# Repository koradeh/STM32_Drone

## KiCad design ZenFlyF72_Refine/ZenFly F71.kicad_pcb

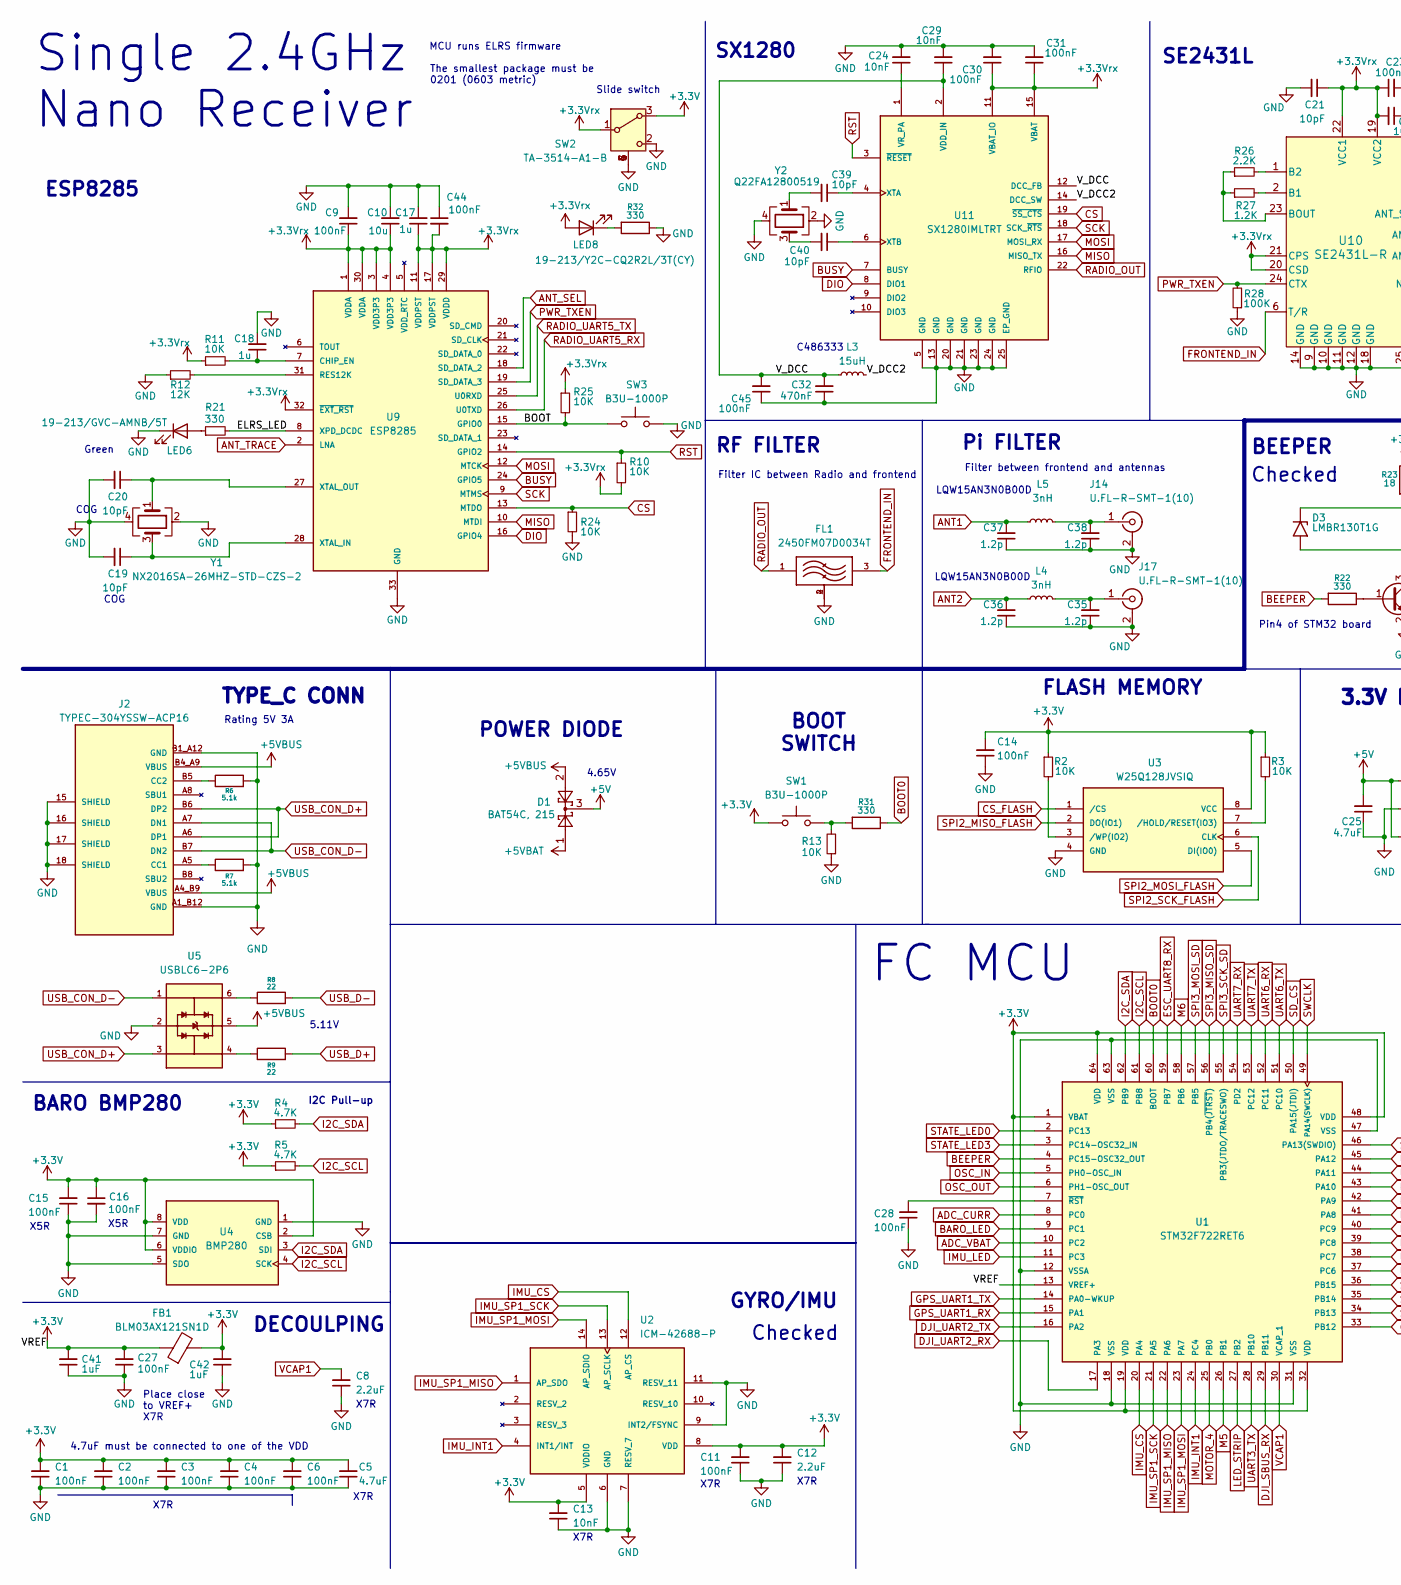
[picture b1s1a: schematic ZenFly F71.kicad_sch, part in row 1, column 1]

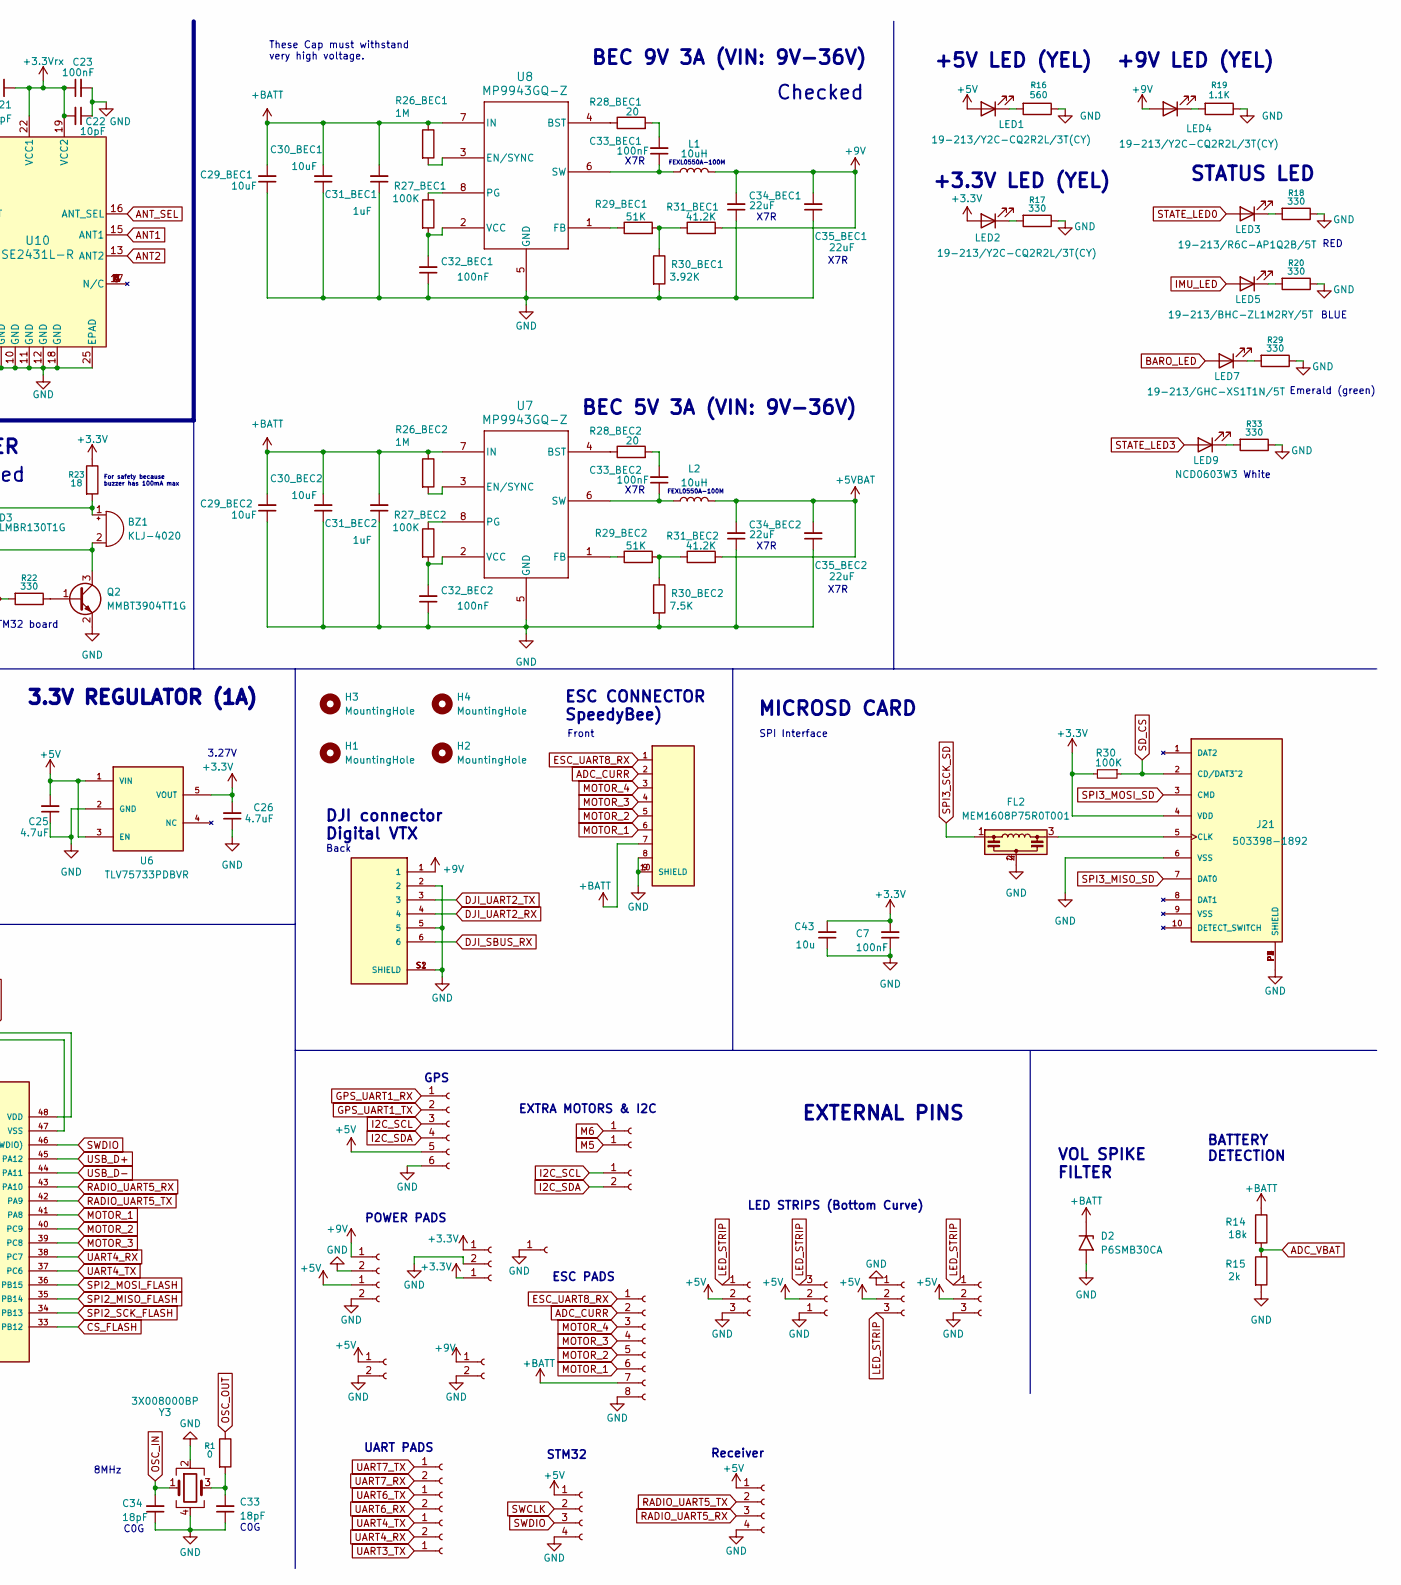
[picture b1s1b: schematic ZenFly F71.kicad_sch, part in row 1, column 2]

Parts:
BZ1: KLJ-4020
C1, C2, C3, C4, C6, C7, C9, C11, C14, C15, C16, C23, C27, C28, C30, C31, C33_BEC1, C33_BEC2, C44, C45: 100nF; C_0201_0603Metric
C5, C25, C26: 4.7uF; C_0603_1608Metric
C8, C12: 2.2uF; C_0402_1005Metric
C10, C43: 10u; C_0603_1608Metric
C13, C24, C29: 10nF; C_0201_0603Metric
C17, C18: 1u; C_0402_1005Metric
C19, C20, C21, C22, C39, C40: 10pF; C_0201_0603Metric
C29_BEC1, C29_BEC2, C30_BEC1, C30_BEC2: 10uF; C_0805_2012Metric
C31_BEC1, C31_BEC2, C41, C42: 1uF; C_0402_1005Metric
C32: 470nF; C_0402_1005Metric
C32_BEC1, C32_BEC2: 100nF; C_0402_1005Metric
C33, C34: 18pF; C_0201_0603Metric
C34_BEC1, C35_BEC1: 22uF; C_0603_1608Metric
C34_BEC2, C35_BEC2: 22uF; C_0402_1005Metric
C35, C36, C37, C38: 1.2p; C_0201_0603Metric
D1: BAT54C, 215; SMD-DIODE-SCHOTTKY-30V-200MA_SOT-23
D2: P6SMB30CA; D_SMB
D3: LMBR130T1G; D_SOD-123
FB1: BLM03AX121SN1D; C_0201_0603Metric
FL1: 2450FM07D0034T; PARTREV 1.2
FL2: MEM1608P75R0T001
H1, H2, H3, H4: MountingHole; MountingHole_3.2mm_M3
J1, J6, J9, J10, J13, J22, J23, J25, J27: Conn_01x02_Socket; SMD_2Pads_Small
J2: TYPEC-304YSSW-ACP16; TYPEC-304-ACP16_XNP; PARTREV A
J3, J18, J19, J20: Conn_01x03_Socket; SMD_3Pads_41mmCurve
J4: SM06B-SRSS-TB_LF__SN_; JST_SM06B-SRSS-TB_LF__SN_
J5, J7: Conn_01x04_Socket; SMD_4Pads_Small
J8: SM08B-SRSS-TB_LF__SN_; SM08B-SRSS-TB_LF_SN
J11: Conn_01x06_Socket; SMD_6Pads_Small
J12, J15, J24, J26, J28: Conn_01x01_Socket; SMD_1Pad_Small
J14, J17: U.FL-R-SMT-1(10); U.FL_Hirose_U.FL-R-SMT-1_Vertical
J16: Conn_01x08_Socket; SMD_8Pads_Small
J21: 503398-1892; MOLEX_503398-1892; PARTREV 0
L1, L2: 10uH; FEXL0550A-100M
L3: 15uH; L_0805_2012Metric
L4, L5: 3nH; L_0402_1005Metric
LED1, LED2, LED4, LED8: 19-213/Y2C-CQ2R2L/3T(CY); LED_0603
LED3: 19-213/R6C-AP1Q2B/5T; LED_0603
LED5: 19-213/BHC-ZL1M2RY/5T; LED_0603
LED6: 19-213/GVC-AMNB/5T; LED_0603
LED7: 19-213/GHC-XS1T1N/5T; LED_0603
LED9: NCD0603W3; LED_0603
Q2: MMBT3904TT1G; TRANS_MMBT3904TT1G
R1: 0; R_0201_0603Metric
R2, R3, R10, R11, R13, R24, R25: 10K; R_0201_0603Metric
R4, R5: 4.7K; R_0201_0603Metric
R6, R7: 5.1k; R_0402_1005Metric
R8, R9: 22; R_0201_0603Metric
R12: 12K; R_0402_1005Metric
R14: 18k; R_0402_1005Metric
R15: 2k; R_0201_0603Metric
R16: 560; R_0201_0603Metric
R17, R18, R20, R21, R22, R29, R31, R32, R33: 330; R_0201_0603Metric
R19: 1.1K; R_0201_0603Metric
R23: 18; R_0201_0603Metric
R26: 2.2K; R_0201_0603Metric
R26_BEC1, R26_BEC2: 1M; R_0402_1005Metric
R27: 1.2K; R_0201_0603Metric
R27_BEC1, R27_BEC2: 100K; R_0402_1005Metric
R28, R30: 100K; R_0201_0603Metric
R28_BEC1, R28_BEC2: 20; R_0402_1005Metric
R29_BEC1, R29_BEC2: 51K; R_0402_1005Metric
R30_BEC1: 3.92K; R_0402_1005Metric
R30_BEC2: 7.5K; R_0402_1005Metric
R31_BEC1, R31_BEC2: 41.2K; R_0402_1005Metric
SW1, SW3: B3U-1000P; SW_B3U-1000P
SW2: TA-3514-A1-B; Slide Switch TA-3514-A1-B
U1: STM32F722RET6
U2: ICM-42688-P; PARTREV 1.2
U3: W25Q128JVSIQ; SOIC127P790X216-8N; PARTREV I
U4: BMP280; XDCR_BMP280; PART_REV 1.19
U5: USBLC6-2P6; PARTREV 5
U6: TLV75733PDBVR; PARTREV Aprill 2011
U7, U8: MP9943GQ-Z; QFN-8_MP9943_MNP
U9: ESP8285; QFN50P500X500X90-33N; PARTREV 2.0
U10: SE2431L-R; SE2431L_SKY-L
U11: SX1280IMLTRT; XCVR_SX1280IMLTRT; PARTREV 3.3
Y1: NX2016SA-26MHZ-STD-CZS-2; Crystal_SMD_2016-4Pin_2.0x1.6mm
Y2: Q22FA12800519; Crystal_SMD_2016-4Pin_2.0x1.6mm
Y3: 3X008000BP; Crystal_SMD_3225-4Pin_3.2x2.5mm

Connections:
+3.3V: C1.2, C2.2, C3.2, C4.2, C5.2, C6.2, C7.2, C11.2, C12.2, C13.2, C14.2, C15.2, C16.1, C26.2, C27.2, C41.2, C42.2, C43.2, FB1.1, FB1.2, J10.1, J15.1, J21.4 (VDD), LED2.E, R2.1, R3.1, R4.1, R5.1, R23.1, R30.2, SW1.1, SW2.3 (A), U1.1 (VBAT), U1.13 (VREF+), U1.19 (VDD), U1.32 (VDD), U1.48 (VDD), U1.64 (VDD), U2.5 (VDDIO), U2.8 (VDD), U3.8 (VCC), U4.2 (CSB), U4.6 (VDDIO), U4.8 (VDD), U6.5 (VOUT)
+3.3Vrx: C9.1, C10.1, C17.1, C21.1, C22.2, C23.1, C30.1, C31.1, C44.2, LED8.E, R10.2, R11.1, R25.1, SW2.1 (B), U9.1 (VDDA), U9.3 (VDD3P3), U9.4 (VDD3P3), U9.11 (VDDPST), U9.17 (VDDPST), U9.29 (VDDD), U9.30 (VDDA), U9.32 (~EXT_RST), U10.19 (VCC2), U10.20 (CSD), U10.21 (CPS), U10.22 (VCC1), U11.11 (VBAT_IO), U11.15 (VBAT)
+5V: C25.2, D1.3, J3.2, J5.1, J7.1, J11.5, J13.1, J18.2, J19.2, J20.2, J27.1, LED1.E, U6.1 (VIN), U6.3 (EN)
+5VBAT: C34_BEC2.2, C35_BEC2.2, D1.1, L2.2, R31_BEC2.2
+5VBUS: D1.2, J2.A4_B9 (VBUS), J2.B4_A9 (VBUS), U5.5
+9V: C34_BEC1.2, C35_BEC1.2, J4.1, J6.1, J22.1, L1.2, LED4.E, R31_BEC1.2
+BATT: C29_BEC1.2, C29_BEC2.2, C30_BEC1.2, C30_BEC2.2, C31_BEC1.2, C31_BEC2.2, D2.1 (A1), J8.7, J16.7, R14.1, R26_BEC1.1, R26_BEC2.1, U7.7 (IN), U8.7 (IN)
/BOOT: R25.2, SW3.1, U9.15 (GPIO0)
/ELRS_LED: R21.2, U9.8 (XPD_DCDC)
/V_DCC: C29.1, C32.2, C45.2, L3.1, U11.2 (VDD_IN), U11.12 (DCC_FB)
/V_DCC2: L3.2, U11.14 (DCC_SW)
ADC_CURR: J8.2, J16.2, U1.8 (PC0)
ADC_VBAT: R14.2, R15.1, U1.10 (PC2)
ANT1: C37.2, L5.1, U10.15 (ANT1)
ANT2: C36.2, L4.1, U10.13 (ANT2)
ANT_SEL: U9.18 (SD_DATA_2), U10.16 (ANT_SEL)
ANT_TRACE: U9.2 (LNA)
BARO_LED: LED7.E, U1.9 (PC1)
BEEPER: R22.2, U1.4 (PC15-OSC32_OUT)
BOOT0: R31.1, U1.60 (BOOT)
BUSY: U9.24 (GPIO5), U11.7 (BUSY)
CS: R24.1, U9.13 (MTDO), U11.19 (~SS_CTS)
CS_FLASH: U1.33 (PB12), U3.1 (/CS)
DIO: U9.16 (GPIO4), U11.8 (DIO1)
DJI_SBUS_RX: J4.6, U1.29 (PB11)
DJI_UART2_RX: J4.4, U1.17 (PA3)
DJI_UART2_TX: J4.3, U1.16 (PA2)
ESC_UART8_RX: J8.1, J16.1, U1.59 (PB7)
FRONTEND_IN: FL1.3, U10.6 (T/R)
GND: C1.1, C2.1, C3.1, C4.1, C5.1, C6.1, C7.1, C8.1, C9.2, C10.2, C11.1, C12.1, C13.1, C14.1, C15.1, C16.2, C17.2, C18.2, C19.2, C20.2, C21.2, C22.1, C23.2, C24.2, C25.1, C26.1, C27.1, C28.1, C29.2, C29_BEC1.1, C29_BEC2.1, C30.2, C30_BEC1.1, C30_BEC2.1, C31.2, C31_BEC1.1, C31_BEC2.1, C32.1, C32_BEC1.1, C32_BEC2.1, C33.1, C34.1, C34_BEC1.1, C34_BEC2.1, C35.1, C35_BEC1.1, C35_BEC2.1, C36.1, C37.1, C38.1, C41.1, C42.1, C43.1, C44.1, C45.1, D2.2 (A2), FL1.2, FL1.4, FL2.2, FL2.4, J2.15 (SHIELD), J2.16 (SHIELD), J2.17 (SHIELD), J2.18 (SHIELD), J2.A1_B12 (GND), J2.B1_A12 (GND), J3.1, J4.2, J4.5, J4.S1 (SHIELD), J4.S2 (SHIELD), J5.4, J6.2, J7.4, J8.8, J8.9 (SHIELD), J8.10 (SHIELD), J10.2, J11.6, J12.1, J13.2, J14.2 (Ext), J16.8, J17.2 (Ext), J18.3, J19.3, J20.1, J21.6 (VSS), J21.P1 (SHIELD), J21.P2 (SHIELD), J21.P3 (SHIELD), J21.P4 (SHIELD), J22.2, J27.2, LED6.C, Q2.2 (E), R6.2, R7.2, R12.1, R13.1, R15.2, R16.1, R17.1, R18.1, R19.1, R20.1, R24.2, R28.1, R29.1, R30_BEC1.2, R30_BEC2.2, R32.1, R33.1, SW2.2 (C), SW2.4 (G), SW2.5 (G), SW2.6 (G), SW2.7 (G), SW3.2, U1.12 (VSSA), U1.18 (VSS), U1.31 (VSS), U1.47 (VSS), U1.63 (VSS), U2.6 (GND), U2.7 (RESV_7), U2.9 (INT2/FSYNC), U2.11 (RESV_11), U3.4 (GND), U4.1 (GND), U4.5 (SDO), U4.7 (GND), U5.2, U6.2 (GND), U7.5 (GND), U8.5 (GND), U9.33 (GND), U10.9 (GND), U10.10 (GND), U10.11 (GND), U10.12 (GND), U10.14 (GND), U10.18 (GND), U10.25 (EPAD), U11.5 (GND), U11.13 (GND), U11.20 (GND), U11.21 (GND), U11.23 (GND), U11.24 (GND), U11.25 (EP_GND), Y1.2, Y1.4, Y2.2, Y2.4, Y3.2, Y3.4
GPS_UART1_RX: J11.1, U1.15 (PA1)
GPS_UART1_TX: J11.2, U1.14 (PA0-WKUP)
I2C_SCL: J1.1, J11.3, R5.2, U1.61 (PB8), U4.4 (SCK)
I2C_SDA: J1.2, J11.4, R4.2, U1.62 (PB9), U4.3 (SDI)
IMU_CS: U1.20 (PA4), U2.12 (AP_CS)
IMU_INT1: U1.24 (PC4), U2.4 (INT1/INT)
IMU_LED: LED5.E, U1.11 (PC3)
IMU_SP1_MISO: U1.22 (PA6), U2.1 (AP_SDO)
IMU_SP1_MOSI: U1.23 (PA7), U2.14 (AP_SDIO)
IMU_SP1_SCK: U1.21 (PA5), U2.13 (AP_SCLK)
LED_STRIP: J3.3, J18.1, J19.1, J20.3, U1.27 (PB2)
M5: J28.1, U1.26 (PB1)
M6: J24.1, U1.58 (PB6)
MISO: U9.10 (MTDI), U11.16 (MISO_TX)
MOSI: U9.12 (MTCK), U11.17 (MOSI_RX)
MOTOR_1: J8.6, J16.6, U1.41 (PA8)
MOTOR_2: J8.5, J16.5, U1.40 (PC9)
MOTOR_3: J8.4, J16.4, U1.39 (PC8)
MOTOR_4: J8.3, J16.3, U1.25 (PB0)
unnamed: BZ1.1 (+), D3.1 (A1), R23.2
unnamed: BZ1.2 (-), D3.2 (A2), Q2.3 (C)
unnamed: C33.2, R1.2, Y3.3
unnamed: C33_BEC1.2, R28_BEC1.2
unnamed: C33_BEC2.2, R28_BEC2.2
unnamed: C39.2, Y2.1
unnamed: C40.2, Y2.3
unnamed: J2.A5 (CC1), R7.1
unnamed: J2.B5 (CC2), R6.1
unnamed: C38.2, J14.1 (In), L5.2
unnamed: C35.2, J17.1 (In), L4.2
unnamed: FL2.3, J21.5 (CLK)
unnamed: LED1.C, R16.2
unnamed: LED2.C, R17.2
unnamed: LED3.C, R18.2
unnamed: LED4.C, R19.2
unnamed: LED5.C, R20.2
unnamed: LED6.E, R21.1
unnamed: LED7.C, R29.2
unnamed: LED8.C, R32.2
unnamed: LED9.C, R33.2
unnamed: Q2.1 (B), R22.1
unnamed: R8.1, U5.6
unnamed: R9.1, U5.4
unnamed: R13.2, R31.2, SW1.2
unnamed: R29_BEC1.2, R30_BEC1.1, R31_BEC1.1
unnamed: R29_BEC2.2, R30_BEC2.1, R31_BEC2.1
unnamed: C28.2, U1.7 (~RST)
unnamed: R3.2, U3.7 (/HOLD/RESET(IO3))
unnamed: R2.2, U3.3 (/WP(IO2))
unnamed: R28_BEC2.1, U7.4 (BST)
unnamed: R26_BEC2.2, U7.3 (EN/SYNC)
unnamed: R29_BEC2.1, U7.1 (FB)
unnamed: R27_BEC2.1, U7.8 (PG)
unnamed: C33_BEC2.1, L2.1, U7.6 (SW)
unnamed: C32_BEC2.2, R27_BEC2.2, U7.2 (VCC)
unnamed: R28_BEC1.1, U8.4 (BST)
unnamed: R26_BEC1.2, U8.3 (EN/SYNC)
unnamed: R29_BEC1.1, U8.1 (FB)
unnamed: R27_BEC1.1, U8.8 (PG)
unnamed: C33_BEC1.1, L1.1, U8.6 (SW)
unnamed: C32_BEC1.2, R27_BEC1.2, U8.2 (VCC)
unnamed: C18.1, R11.2, U9.7 (CHIP_EN)
unnamed: R12.2, U9.31 (RES12K)
unnamed: C19.1, U9.28 (XTAL_IN), Y1.3
unnamed: C20.1, U9.27 (XTAL_OUT), Y1.1
unnamed: R27.2, U10.2 (B1)
unnamed: R26.2, U10.1 (B2)
unnamed: R26.1, R27.1, U10.23 (BOUT)
unnamed: C24.1, U11.1 (VR_PA)
unnamed: C39.1, U11.4 (XTA)
unnamed: C40.1, U11.6 (XTB)
OSC_IN: C34.2, U1.5 (PH0-OSC_IN), Y3.1
OSC_OUT: R1.1, U1.6 (PH1-OSC_OUT)
PWR_TXEN: R28.2, U9.19 (SD_DATA_3), U10.24 (CTX)
RADIO_OUT: FL1.1, U11.22 (RFIO)
RADIO_UART5_RX: J5.3, U1.43 (PA10), U9.26 (U0TXD)
RADIO_UART5_TX: J5.2, U1.42 (PA9), U9.25 (U0RXD)
RST: R10.1, U9.14 (GPIO2), U11.3 (~RESET)
SCK: U9.9 (MTMS), U11.18 (SCK_~RTS)
SD_CS: J21.2 (CD/DAT3^2), R30.1, U1.50 (PA15(JTDI))
SPI2_MISO_FLASH: U1.35 (PB14), U3.2 (DO(IO1))
SPI2_MOSI_FLASH: U1.36 (PB15), U3.5 (DI(IO0))
SPI2_SCK_FLASH: U1.34 (PB13), U3.6 (CLK)
SPI3_MISO_SD: J21.7 (DAT0), U1.56 (PB4(~JTRST))
SPI3_MOSI_SD: J21.3 (CMD), U1.57 (PB5)
SPI3_SCK_SD: FL2.1, U1.55 (PB3(JTDO/TRACESWO))
STATE_LED0: LED3.E, U1.2 (PC13)
STATE_LED3: LED9.E, U1.3 (PC14-OSC32_IN)
SWCLK: J7.2, U1.49 (PA14(SWCLK))
SWDIO: J7.3, U1.46 (PA13(SWDIO))
UART3_TX: J26.1, U1.28 (PB10)
UART4_RX: J25.2, U1.38 (PC7)
UART4_TX: J25.1, U1.37 (PC6)
UART6_RX: J23.2, U1.52 (PC11)
UART6_TX: J23.1, U1.51 (PC10)
UART7_RX: J9.2, U1.54 (PD2)
UART7_TX: J9.1, U1.53 (PC12)
USB_CON_D+: J2.A6 (DP1), J2.B6 (DP2), U5.3
USB_CON_D-: J2.A7 (DN1), J2.B7 (DN2), U5.1
USB_D+: R9.2, U1.45 (PA12)
USB_D-: R8.2, U1.44 (PA11)
VCAP1: C8.2, U1.30 (VCAP_1)

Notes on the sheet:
LQW15AN3N0B00D
Rating 5V 3A
ESC CONNECTOR SpeedyBee)
Checked
X7R
Pin4 of STM32 board
+3.3V LED (YEL)
UART PADS
Single 2.4GHz Nano Receiver
BLUE
Place close to VREF+ X7R
RF FILTER
STM32
SX1280
FEXL0550A-100M
SE2431L
C486333
STATUS LED
White
X5R
BEC 5V 3A (VIN: 9V-36V)
Back
These Cap must withstand very high voltage.
LED STRIPS (Bottom Curve)
Filter IC between Radio and frontend
Emerald (green)
EXTERNAL PINS
BEC 9V 3A (VIN: 9V-36V)
C0G
COG
5.11V
POWER DIODE
Receiver
4.65V
BOOT SWITCH
Front
DECOULPING
GPS
+9V LED (YEL)
Filter between frontend and antennas

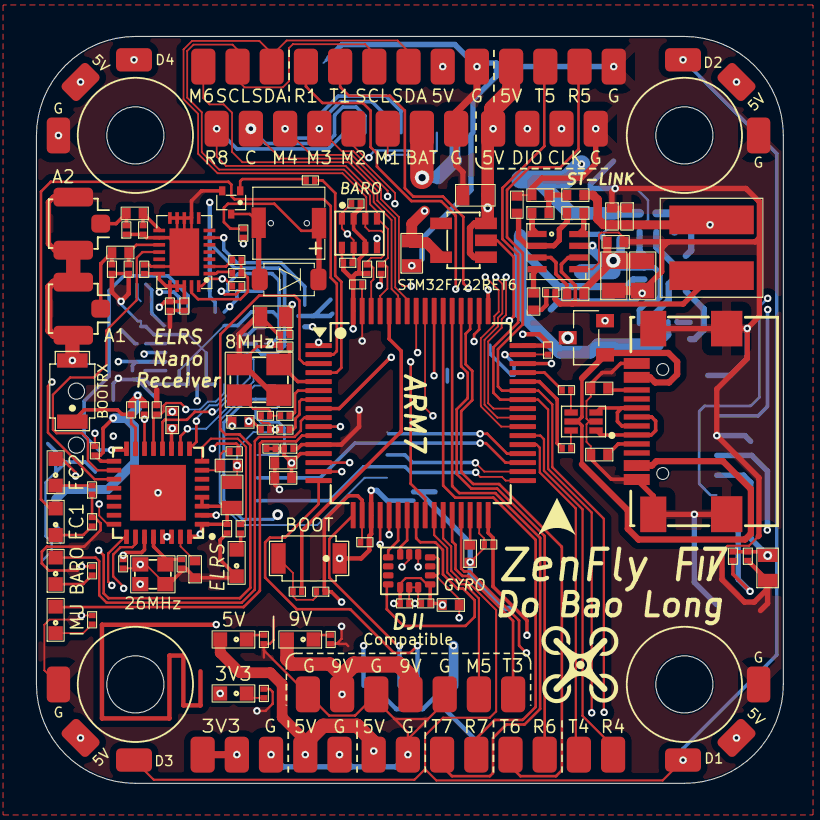
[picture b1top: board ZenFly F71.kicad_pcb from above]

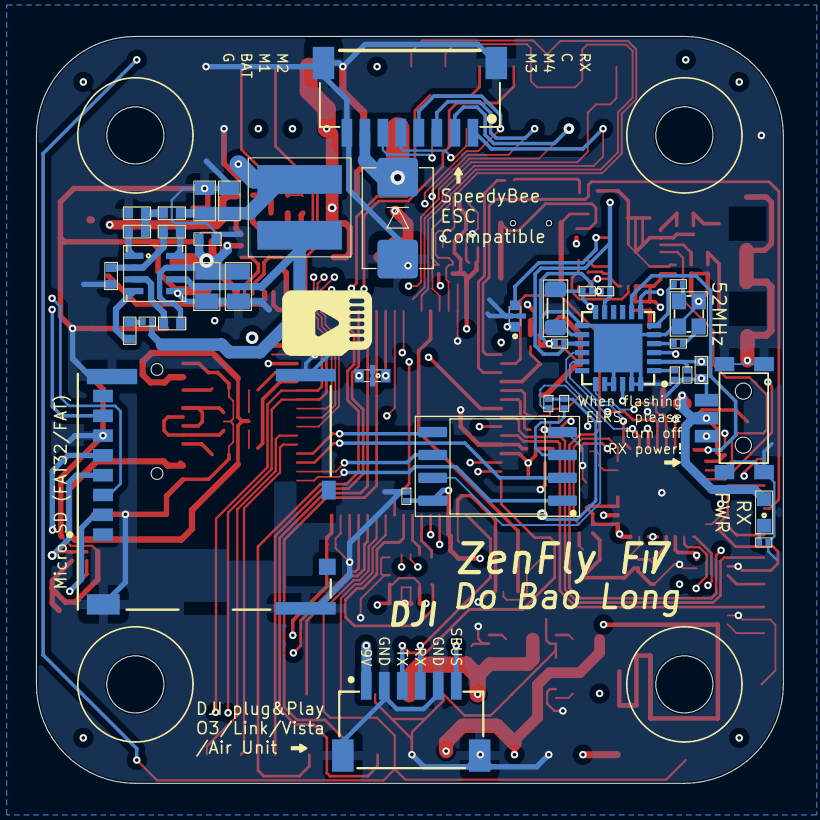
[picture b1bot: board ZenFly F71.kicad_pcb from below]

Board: 4 copper layers, 41.5 x 41.5 mm, 175 parts (39 on the bottom side), 131 nets.

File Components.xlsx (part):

Resistor | Value | LCSC | Footprint | Spec
R1 | 0 | None | #0201 | None
R2 | 10K | C319932 | #0201 | 1/32W Thin Film Resistor 15V ±0.5% ±50ppm/℃ 10kΩ 0201 Chip Resistor - Surface M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
R3 | 10K | C319932 | #0201 | 1/32W Thin Film Resistor 15V ±0.5% ±50ppm/℃ 10kΩ 0201 Chip Resistor - Surface M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
R4 | 4.7K | C852254 | #0201 | 50mW Thin Film Resistor ±25ppm/℃ ±0.1% 4.7kΩ 0201 Chip Resistor - Surface Mount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
R5 | 4.7K | C852254 | #0201 | 50mW Thin Film Resistor ±25ppm/℃ ±0.1% 4.7kΩ 0201 Chip Resistor - Surface Mount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
R6 | 5.1K | C851767 | #0402 | 50mW Thick Film Resistors ±0.5% ±200ppm/℃ 5.1kΩ 0201 Chip Resistor - Surface Mo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
R7 | 5.1K | C851767 | #0201 | 50mW Thick Film Resistors ±0.5% ±200ppm/℃ 5.1kΩ 0201 Chip Resistor - Surface Mo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
R8 | 22 | C2991382 | #0201 | 1/20W Thick Film Resistors 25V ±100ppm/℃ ±1% 22Ω 0201 Chip Resistor - Surface M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
R9 | 22 | C2991382 | #0201 | 1/20W Thick Film Resistors 25V ±100ppm/℃ ±1% 22Ω 0201 Chip Resistor - Surface M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
R10 | 10K | C319932 | #0201 | 1/32W Thin Film Resistor 15V ±0.5% ±50ppm/℃ 10kΩ 0201 Chip Resistor - Surface M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
R11 | 10K | C319932 | #0201 | 1/32W Thin Film Resistor 15V ±0.5% ±50ppm/℃ 10kΩ 0201 Chip Resistor - Surface M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
R12 | 12K | C2693077 | #0402 | 50mW 25V ±100ppm/℃ ±1% 12kΩ 0201 Chip Resistor - Surface Mount ROHS
R13 | 10K | C319932 | #0201 | 1/32W Thin Film Resistor 15V ±0.5% ±50ppm/℃ 10kΩ 0201 Chip Resistor - Surface M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
R14 | 18K | C246974 | #0402 | 1/16W Thin Film Resistor 50V ±25ppm/℃ ±0.1% 18kΩ 0402 Chip Resistor - Surface M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
R15 | 2K | C490810 | #0201 | 0.05W Thin Film Resistor 25V ±0.1% ±25ppm/℃ 2kΩ 0201 Chip Resistor - Surface Mo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
R16 | 560 | C490810 | #0201 | 0.05W Thin Film Resistor 25V ±0.1% ±25ppm/℃ 2kΩ 0201 Chip Resistor - Surface Mo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
R17 | 330 | C274872 | #0201 | 50mW Thick Film Resistors 25V ±1% ±200ppm/℃ 330Ω 0201 Chip Resistor - Surface M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
R18 | 330 | C274872 | #0201 | 50mW Thick Film Resistors 25V ±1% ±200ppm/℃ 330Ω 0201 Chip Resistor - Surface M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
R19 | 1.1K | C490809 | #0201 | 0.05W Thin Film Resistor 25V ±0.1% ±25ppm/℃ 1.1kΩ 0201 Chip Resistor - Surface 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
R20 | 330 | C274872 | #0201 | 50mW Thick Film Resistors 25V ±1% ±200ppm/℃ 330Ω 0201 Chip Resistor - Surface M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
R21 | 330 | C274872 | #0201 | 50mW Thick Film Resistors 25V ±1% ±200ppm/℃ 330Ω 0201 Chip Resistor - Surface M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
R22 | 330 | C274872 | #0201 | 50mW Thick Film Resistors 25V ±1% ±200ppm/℃ 330Ω 0201 Chip Resistor - Surface M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
R23 | 18 | C384425 | #0201 | 50mW 25V ±100ppm/℃ ±1% 18Ω 0201 Chip Resistor - Surface Mount ROHS
R24 | 10K | C319932 | #0201 | 1/32W Thin Film Resistor 15V ±0.5% ±50ppm/℃ 10kΩ 0201 Chip Resistor - Surface M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
R25 | 10K | C319932 | #0201 | 1/32W Thin Film Resistor 15V ±0.5% ±50ppm/℃ 10kΩ 0201 Chip Resistor - Surface M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
R26 | 2.2K | C2074393 | #0201 | 50mW Thick Film Resistors 30V ±1% ±100ppm/℃ 2.2kΩ 0201 Chip Resistor - Surface 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
R27 | 1.2K | C319992 | #0201 | 1/32W Thin Film Resistor 15V ±0.5% ±50ppm/℃ 1.2kΩ 0201 Chip Resistor - Surface 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
R28 | 100K | C2108139 | #0201 | 50mW Thick Film Resistors 15V ±1% ±200ppm/℃ 100kΩ 0201 Chip Resistor - Surface 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
R29 | 330 | C274872 | #0201 | 50mW Thick Film Resistors 25V ±1% ±200ppm/℃ 330Ω 0201 Chip Resistor - Surface M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
R30 | 100K | C2108139 | #0201 | 50mW Thick Film Resistors 15V ±1% ±200ppm/℃ 100kΩ 0201 Chip Resistor - Surface 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
R31_BEC2 | 41.2K | C2683018 | #0402 | 1/16W Thin Film Resistor 50V ±25ppm/℃ ±0.1% 41.2kΩ 0402 Chip Resistor - Surface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
R31_BEC1 | 41.2K | C2683018 | #0402 | 1/16W Thin Film Resistor 50V ±25ppm/℃ ±0.1% 41.2kΩ 0402 Chip Resistor - Surface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
R30_BEC2 | 7.5K | C728565 | #0402 | 62.5mW Thin Film Resistor 50V ±25ppm/℃ ±0.1% 7.5kΩ 0402 Chip Resistor - Surface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
R30_BEC1 | 3.92K | C284551 | #0402 | 1/16W Thin Film Resistor 50V ±25ppm/℃ ±1% 3.92kΩ 0402 Chip Resistor - Surface M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
R29_BEC2 | 51K | C284600 | #0402 | 1/16W Thin Film Resistor 50V ±25ppm/℃ ±1% 51kΩ 0402 Chip Resistor - Surface Mou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
R29_BEC1 | 51K | C284600 | #0402 | 1/16W Thin Film Resistor 50V ±25ppm/℃ ±1% 51kΩ 0402 Chip Resistor - Surface Mou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
R28_BEC2 | 20 | C2686477 | #0402 | 1/16W Thin Film Resistor 50V ±0.5% ±25ppm/℃ 20Ω 0402 Chip Resistor - Surface Mo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
R28_BEC1 | 20 | C2686477 | #0402 | 1/16W Thin Film Resistor 50V ±0.5% ±25ppm/℃ 20Ω 0402 Chip Resistor - Surface Mo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
R27_BEC2 | 100K | C852472 | #0402 | 62.5mW Thin Film Resistor 50V ±25ppm/℃ ±0.1% 100kΩ 0402 Chip Resistor - Surface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
R27_BEC1 | 100K | C852472 | #0402 | 62.5mW Thin Film Resistor 50V ±25ppm/℃ ±0.1% 100kΩ 0402 Chip Resistor - Surface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
R26_BEC2 | 1M | C1884615 | #0402 | 100mW Thin Film Resistor 50V ±50ppm/℃ ±1% 1MΩ 0402 Chip Resistor - Surface Moun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
R26_BEC1 | 1M | C1884615 | #0402 | 100mW Thin Film Resistor 50V ±50ppm/℃ ±1% 1MΩ 0402 Chip Resistor - Surface Moun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
Capacitor | Value | LCSC | Footprint | Spec
C1 | 100nF | C161494 | #0201 | 10V 100nF X7R ±10% 0201 Multilayer Ceramic Capacitors MLCC - SMD/SMT ROHS
C2 | 100nF | C161494 | #0201 | 10V 100nF X7R ±10% 0201 Multilayer Ceramic Capacitors MLCC - SMD/SMT ROHS
C3 | 100nF | C161494 | #0201 | 10V 100nF X7R ±10% 0201 Multilayer Ceramic Capacitors MLCC - SMD/SMT ROHS
C4 | 100nF | C161494 | #0201 | 10V 100nF X7R ±10% 0201 Multilayer Ceramic Capacitors MLCC - SMD/SMT ROHS
C5 | 4.7uF | C913474 | #0603 | 10V 4.7uF X7R ±10% 0603 Multilayer Ceramic Capacitors MLCC - SMD/SMT ROHS
C6 | 100nF | C161494 | #0201 | 10V 100nF X7R ±10% 0201 Multilayer Ceramic Capacitors MLCC - SMD/SMT ROHS
C7 | 100nF | C161494 | #0201 | 10V 100nF X7R ±10% 0201 Multilayer Ceramic Capacitors MLCC - SMD/SMT ROHS
C8 | 2.2uF | C2997286 | #0402 | 10V 2.2uF X7R ±10% 0402 Multilayer Ceramic Capacitors MLCC - SMD/SMT ROHS
C9 | 100nF | C161494 | #0201 | 10V 100nF X7R ±10% 0201 Multilayer Ceramic Capacitors MLCC - SMD/SMT ROHS
C10 | 10uF | C2959727 | #0603 | 10V 10uF X7R ±10% 0603 Multilayer Ceramic Capacitors MLCC - SMD/SMT ROHS
C11 | 100nF | C161494 | #0201 | 10V 100nF X7R ±10% 0201 Multilayer Ceramic Capacitors MLCC - SMD/SMT ROHS
C12 | 2.2uF | C2997286 | #0402 | 10V 2.2uF X7R ±10% 0402 Multilayer Ceramic Capacitors MLCC - SMD/SMT ROHS
C13 | 10nF | C6049498 | #0201 | 10V 10nF X7R ±5% 0201 Multilayer Ceramic Capacitors MLCC - SMD/SMT ROHS
C14 | 100nF | C161494 | #0201 | 10V 100nF X7R ±10% 0201 Multilayer Ceramic Capacitors MLCC - SMD/SMT ROHS
C15 | 100nF | C161494 | #0201 | 10V 100nF X7R ±10% 0201 Multilayer Ceramic Capacitors MLCC - SMD/SMT ROHS
C16 | 100nF | C161494 | #0201 | 10V 100nF X7R ±10% 0201 Multilayer Ceramic Capacitors MLCC - SMD/SMT ROHS
C17 | 1uF | C528974 | #0402 | 10V 1uF X7R ±10% 0402 Multilayer Ceramic Capacitors MLCC - SMD/SMT ROHS
C18 | 1uF | C528974 | #0402 | 10V 1uF X7R ±10% 0402 Multilayer Ceramic Capacitors MLCC - SMD/SMT ROHS
C19 | 10pF | C18213215 | #0201 | 16V 10pF C0G ±5% 0201 Multilayer Ceramic Capacitors MLCC - SMD/SMT ROHS
C20 | 10pF | C18213215 | #0201 | 16V 10pF C0G ±5% 0201 Multilayer Ceramic Capacitors MLCC - SMD/SMT ROHS
C21 | 10pF | C18213215 | #0201 | 16V 10pF C0G ±5% 0201 Multilayer Ceramic Capacitors MLCC - SMD/SMT ROHS
C22 | 10pF | C18213215 | #0201 | 16V 10pF C0G ±5% 0201 Multilayer Ceramic Capacitors MLCC - SMD/SMT ROHS
C23 | 100nF | C161494 | #0201 | 10V 100nF X7R ±10% 0201 Multilayer Ceramic Capacitors MLCC - SMD/SMT ROHS
C24 | 10nF | C6049498 | #0201 | 10V 10nF X7R ±5% 0201 Multilayer Ceramic Capacitors MLCC - SMD/SMT ROHS
C25 | 4.7uF | C913474 | #0603 | 10V 4.7uF X7R ±10% 0603 Multilayer Ceramic Capacitors MLCC - SMD/SMT ROHS
C26 | 4.7uF | C913474 | #0603 | 10V 4.7uF X7R ±10% 0603 Multilayer Ceramic Capacitors MLCC - SMD/SMT ROHS
C27 | 100nF | C161494 | #0201 | 10V 100nF X7R ±10% 0201 Multilayer Ceramic Capacitors MLCC - SMD/SMT ROHS
C28 | 100nF | C161494 | #0201 | 10V 100nF X7R ±10% 0201 Multilayer Ceramic Capacitors MLCC - SMD/SMT ROHS
C29 | 10nF | C6049498 | #0201 | 10V 10nF X7R ±5% 0201 Multilayer Ceramic Capacitors MLCC - SMD/SMT ROHS
C30 | 100nF | C161494 | #0201 | 10V 100nF X7R ±10% 0201 Multilayer Ceramic Capacitors MLCC - SMD/SMT ROHS
C31 | 100nF | C161494 | #0201 | 10V 100nF X7R ±10% 0201 Multilayer Ceramic Capacitors MLCC - SMD/SMT ROHS
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
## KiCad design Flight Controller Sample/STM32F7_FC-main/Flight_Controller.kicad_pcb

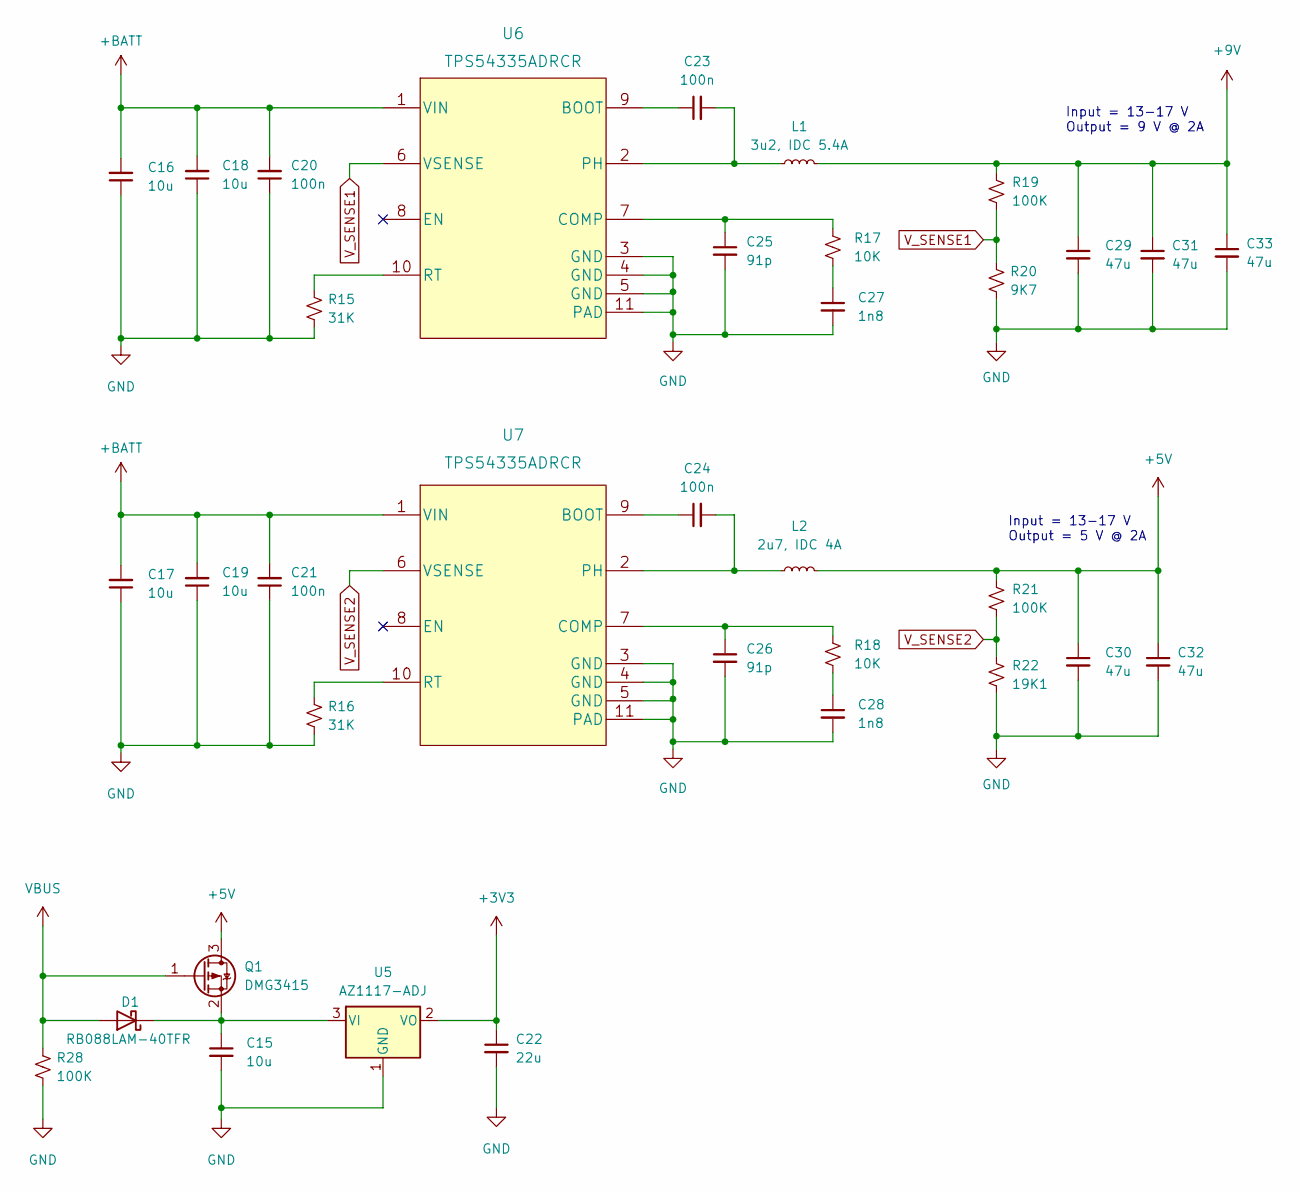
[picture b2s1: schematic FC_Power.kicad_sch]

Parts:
C15, C16, C17, C18, C19: 10u; C_0805_2012Metric
C20, C21, C23, C24: 100n; C_0402_1005Metric
C22: 22u; C_0805_2012Metric
C25, C26: 91p; C_0201_0603Metric
C27, C28: 1n8; C_0603_1608Metric
C29, C30, C31, C32, C33: 47u; C_1210_3225Metric
D1: RB088LAM-40TFR; D_SOD-123
L1: 3u2, IDC 5.4A; MDE0530-6R8M
L2: 2u7, IDC 4A; MDE0530-6R8M
Q1: DMG3415; SOT-23
R15, R16: 31K; R_0402_1005Metric
R17, R18: 10K; R_0402_1005Metric
R19: 100K; R_0402_1005Metric
R20: 9K7; R_0402_1005Metric
R21, R28: 100K; R_0201_0603Metric
R22: 19K1; R_0201_0603Metric
U5: AZ1117-ADJ; SOT-223-3_TabPin2
U6, U7: TPS54335ADRCR

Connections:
+3V3: C22.1, U5.2 (VO); also elsewhere on the board
+5V: C30.1, C32.1, L2.2, Q1.3 (D), R21.1; also elsewhere on the board
+9V: C29.1, C31.1, C33.1, L1.2, R19.1; also elsewhere on the board
+BATT: C16.2, C17.2, C18.2, C19.2, C20.2, C21.2, U6.1 (VIN), U7.1 (VIN); also elsewhere on the board
GND: C15.2, C16.1, C17.1, C18.1, C19.1, C20.1, C21.1, C22.2, C25.2, C26.2, C27.2, C28.2, C29.2, C30.2, C31.2, C32.2, C33.2, R15.2, R16.2, R20.2, R22.2, R28.2, U5.1 (GND), U6.3 (GND), U6.4 (GND), U6.5 (GND), U6.11 (PAD), U7.3 (GND), U7.4 (GND), U7.5 (GND), U7.11 (PAD); also elsewhere on the board
unnamed: C15.1, D1.1 (K), Q1.2 (S), U5.3 (VI)
unnamed: C23.1, U6.9 (BOOT)
unnamed: C23.2, L1.1, U6.2 (PH)
unnamed: C24.1, U7.9 (BOOT)
unnamed: C24.2, L2.1, U7.2 (PH)
unnamed: C25.1, R17.1, U6.7 (COMP)
unnamed: C26.1, R18.1, U7.7 (COMP)
unnamed: C27.1, R17.2
unnamed: C28.1, R18.2
unnamed: R15.1, U6.10 (RT)
unnamed: R16.1, U7.10 (RT)
VBUS: D1.2 (A), Q1.1 (G), R28.1; also elsewhere on the board
V_SENSE1: R19.2, R20.1, U6.6 (VSENSE)
V_SENSE2: R21.2, R22.1, U7.6 (VSENSE)

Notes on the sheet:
Input = 13-17 V Output = 9 V @ 2A
Input = 13-17 V Output = 5 V @ 2A

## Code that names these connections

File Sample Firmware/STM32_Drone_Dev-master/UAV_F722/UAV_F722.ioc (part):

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Mcu.Name=STM32F722R(C-E)Tx
Mcu.Package=LQFP64
Mcu.UserName=STM32F722RETx
PA0-WKUP.Mode=Asynchronous
PA0-WKUP.Signal=UART4_TX
PA1.Mode=Asynchronous
PA1.Signal=UART4_RX
PA2.GPIOParameters=GPIO_Label
PA2.GPIO_Label=UART2_TX_LiDar
PA2.Mode=Asynchronous
PA2.Signal=USART2_TX
PA3.GPIOParameters=GPIO_Label
PA3.GPIO_Label=UART2_RX_LiDar
PA3.Mode=Asynchronous
PA3.Signal=USART2_RX
PA4.GPIOParameters=GPIO_Speed,PinState,GPIO_Label
PA4.GPIO_Label=SPI1_CS
PA4.GPIO_Speed=GPIO_SPEED_FREQ_VERY_HIGH
PA4.PinState=GPIO_PIN_SET
PA4.Signal=GPIO_Output
PA5.Mode=Full_Duplex_Master
PA5.Signal=SPI1_SCK
PA6.Mode=Full_Duplex_Master
PA6.Signal=SPI1_MISO
PA7.Mode=Full_Duplex_Master
PA7.Signal=SPI1_MOSI
PA8.Signal=S_TIM1_CH1
PA9.Signal=S_TIM1_CH2
PB2.GPIOParameters=GPIO_Label
PB2.GPIO_Label=Beeper_Out
PB2.Signal=GPIO_Output
PB3.Signal=GPIO_Output
PB6.Mode=Asynchronous
PB6.Signal=USART1_TX
PB7.Mode=Asynchronous
PB7.Signal=USART1_RX
PB8.Mode=I2C
PB8.Signal=I2C1_SCL
PB9.Mode=I2C
PB9.Signal=I2C1_SDA
PC0.GPIOParameters=GPIO_ModeDefaultEXTI
PC0.GPIO_ModeDefaultEXTI=GPIO_MODE_IT_FALLING
PC0.Signal=GPXTI0
PC1.Signal=ADCx_IN11
PC12.Mode=Asynchronous
PC12.Signal=UART5_TX
PC14-OSC32_IN.GPIOParameters=PinState
PC14-OSC32_IN.PinState=GPIO_PIN_SET
PC14-OSC32_IN.Signal=GPIO_Output
PC15-OSC32_OUT.GPIOParameters=PinState
PC15-OSC32_OUT.PinState=GPIO_PIN_SET
PC15-OSC32_OUT.Signal=GPIO_Output
PC4.GPIOParameters=GPIO_ModeDefaultEXTI
PC4.GPIO_ModeDefaultEXTI=GPIO_MODE_IT_FALLING
PC4.Signal=GPXTI4
PC8.Signal=S_TIM3_CH3
PC9.Signal=S_TIM3_CH4
PD2.Mode=Asynchronous
PD2.Signal=UART5_RX
PH0-OSC_IN.Mode=HSE-External-Oscillator
PH0-OSC_IN.Signal=RCC_OSC_IN
PH1-OSC_OUT.Mode=HSE-External-Oscillator
PH1-OSC_OUT.Signal=RCC_OSC_OUT
RCC.HSE_VALUE=8000000
RCC.SYSCLKFreq_VALUE=216000000
RCC.SYSCLKSource=RCC_SYSCLKSOURCE_PLLCLK
board=custom

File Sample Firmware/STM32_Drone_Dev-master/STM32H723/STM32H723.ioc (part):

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Mcu.Name=STM32H723ZGTx
Mcu.Package=LQFP144
Mcu.UserName=STM32H723ZGTx
PA0.GPIOParameters=GPIO_Label
PA0.GPIO_Label=UART4_TX_GPS
PA0.Mode=Asynchronous
PA0.Signal=UART4_TX
PA1.GPIOParameters=GPIO_Label
PA1.GPIO_Label=UART4_RX_GPS
PA1.Mode=Asynchronous
PA1.Signal=UART4_RX
PA10.GPIOParameters=GPIO_Speed
PA10.GPIO_Speed=GPIO_SPEED_FREQ_VERY_HIGH
PA10.Mode=Asynchronous
PA10.Signal=USART1_RX
PA11.Mode=Device_Only_FS
PA11.Signal=USB_OTG_HS_DM
PA12.Mode=Device_Only_FS
PA12.Signal=USB_OTG_HS_DP
PA13(JTMS/SWDIO).Mode=Trace_Asynchronous_SW
PA13(JTMS/SWDIO).Signal=DEBUG_JTMS-SWDIO
PA14(JTCK/SWCLK).Mode=Trace_Asynchronous_SW
PA14(JTCK/SWCLK).Signal=DEBUG_JTCK-SWCLK
PA2.Mode=Asynchronous
PA2.Signal=USART2_TX
PA3.Mode=Asynchronous
PA3.Signal=USART2_RX
PA5.Signal=S_TIM2_CH1_ETR
PA7.Signal=S_TIM3_CH2
PA9.GPIOParameters=GPIO_Speed
PA9.GPIO_Speed=GPIO_SPEED_FREQ_VERY_HIGH
PA9.Mode=Asynchronous
PA9.Signal=USART1_TX
PB1.Signal=S_TIM3_CH4
PB10.Signal=S_TIM2_CH3
PB12.Mode=Asynchronous
PB12.Signal=UART5_RX
PB13.Mode=Asynchronous
PB13.Signal=UART5_TX
PB3(JTDO/TRACESWO).Mode=Trace_Asynchronous_SW
PB3(JTDO/TRACESWO).Signal=DEBUG_JTDO-SWO
PB5.GPIOParameters=GPIO_Label
PB5.GPIO_Label=IMU_INT
PB5.Signal=GPIO_Input
PB6.Mode=I2C
PB6.Signal=I2C1_SCL
PB7.Mode=I2C
PB7.Signal=I2C1_SDA
PC14-OSC32_IN.Mode=LSE-External-Oscillator
PC14-OSC32_IN.Signal=RCC_OSC32_IN
PC15-OSC32_OUT.Mode=LSE-External-Oscillator
PC15-OSC32_OUT.Signal=RCC_OSC32_OUT
PF10.Mode=O1_P1_CLK
PF10.Signal=OCTOSPIM_P1_CLK
PF11.Mode=IN2-Single-Ended
PF11.Signal=ADC1_INP2
PF6.Mode=OCTOSPI1_IOL_Port1L
PF6.Signal=OCTOSPIM_P1_IO3
PF7.Mode=OCTOSPI1_IOL_Port1L
PF7.Signal=OCTOSPIM_P1_IO2
PF8.Mode=OCTOSPI1_IOL_Port1L
PF8.Signal=OCTOSPIM_P1_IO0
PF9.Mode=OCTOSPI1_IOL_Port1L
PF9.Signal=OCTOSPIM_P1_IO1
PG10.GPIOParameters=GPIO_Speed
PG10.GPIO_Speed=GPIO_SPEED_FREQ_VERY_HIGH
PG10.Signal=DCMI_D2
PG11.GPIOParameters=GPIO_Speed
PG11.GPIO_Speed=GPIO_SPEED_FREQ_VERY_HIGH
PG11.Signal=DCMI_D3
PG13.GPIOParameters=GPIO_Speed
PG13.GPIO_Speed=GPIO_SPEED_FREQ_VERY_HIGH
PG13.Signal=SPI6_SCK
PG14.GPIOParameters=GPIO_Speed
PG14.GPIO_Speed=GPIO_SPEED_FREQ_VERY_HIGH
PG14.Signal=SPI6_MOSI
PG2.Signal=GPXTI2
PG6.Mode=OCTOSPI1_Port1_NCS
PG6.Signal=OCTOSPIM_P1_NCS
PG7.GPIOParameters=GPIO_Speed,PinState,GPIO_PuPd,GPIO_Label,GPIO_ModeDefaultOutputPP
PG7.GPIO_Label=LED_Blue
PG7.GPIO_ModeDefaultOutputPP=GPIO_MODE_OUTPUT_PP
PG7.GPIO_PuPd=GPIO_NOPULL
PG7.GPIO_Speed=GPIO_SPEED_FREQ_HIGH
PG7.PinState=GPIO_PIN_SET
PG7.Signal=GPIO_Output
PG8.GPIOParameters=GPIO_Speed
PG8.GPIO_Speed=GPIO_SPEED_FREQ_VERY_HIGH
PG8.Signal=SPI6_NSS
PH0-OSC_IN.Mode=HSE-External-Oscillator
PH0-OSC_IN.Signal=RCC_OSC_IN
PH1-OSC_OUT.Mode=HSE-External-Oscillator
PH1-OSC_OUT.Signal=RCC_OSC_OUT
RCC.HSE_VALUE=25000000
RCC.SYSCLKFreq_VALUE=550000000
RCC.SYSCLKSource=RCC_SYSCLKSOURCE_PLLCLK
board=custom
